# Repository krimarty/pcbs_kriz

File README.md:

# pcbs_kriz
Repository for all of Martin's PCBs

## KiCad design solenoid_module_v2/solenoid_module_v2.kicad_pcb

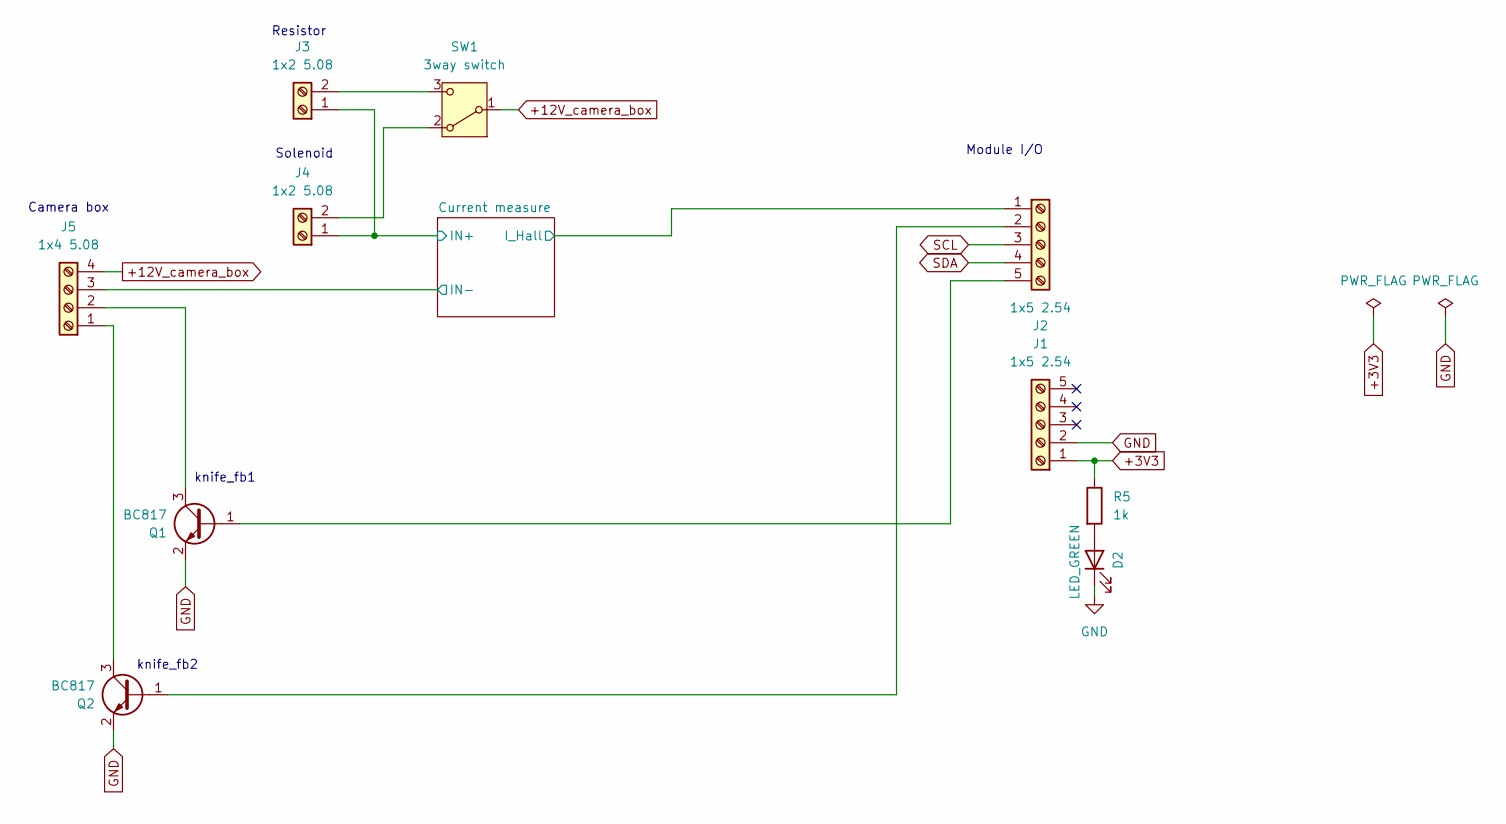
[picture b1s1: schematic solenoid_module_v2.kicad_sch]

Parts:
D2: LED_GREEN; LED_0805_2012Metric_Pad1.15x1.40mm_HandSolder; Manufacturer Part Number APTD2012LCGCK; Mouser number 604-APTD2012LCGCK
J1, J2: 1x5 2.54; PinHeader_1x05_P2.54mm_Vertical; Manufacturer Part Number 68000-420HLF; Mouser Part Number 649-68000-420HLF
J3, J4: 1x2 5.08; TerminalBlock_MetzConnect_Type101_RT01602HBWC_1x02_P5.08mm_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; Manufacturer Part Number TB0012-508-02GR; Mouser Part Number 179-TB0012-508-02GR
J5: 1x4 5.08; TerminalBlock_MetzConnect_Type101_RT01604HBWC_1x04_P5.08mm_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; Manufacturer Part Number TB0012-508-02GR; Mouser Part Number 179-TB0012-508-02GR
Q1, Q2: BC817; SOT-23; Manufacturer Part Number BC817; Mouser Part Number 583-BC817
R5: 1k; R_0603_1608Metric_Pad0.98x0.95mm_HandSolder; Manufacturer Part Number RC0603FR-071KL; Mouser number 603-RC0603FR-071KL
SW1: 3way switch; SW_Slide-03_Wuerth-WS-SLTV_10x2.5x6.4_P2.54mm; Manufacturer Part Number 200AWMSP3T2A1M2QE; Mouser Part Number 612-200AWMSP3T2A1M2Q

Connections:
+3V3: J1.1, R5.1; also elsewhere on the board
+12V_camera_box: J5.4, SW1.1 (B)
/Current measure/IN+: J3.1, J4.1; also elsewhere on the board
/Current measure/IN-: J5.3; also elsewhere on the board
/Current measure/I_Hall: J2.1; also elsewhere on the board
GND: D2.1 (K), J1.2, Q1.2 (E), Q2.2 (E); also elsewhere on the board
unnamed: D2.2 (A), R5.2
unnamed: J2.2, Q2.1 (B)
unnamed: J2.5, Q1.1 (B)
unnamed: J3.2, SW1.3 (C)
unnamed 10: J4.2, SW1.2 (A); also elsewhere on the board
unnamed: J5.1, Q2.3 (C)
unnamed: J5.2, Q1.3 (C)
SCL: J2.3
SDA: J2.4

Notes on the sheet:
Solenoid
knife_fb1
knife_fb2
Module I/O
Resistor
Camera box

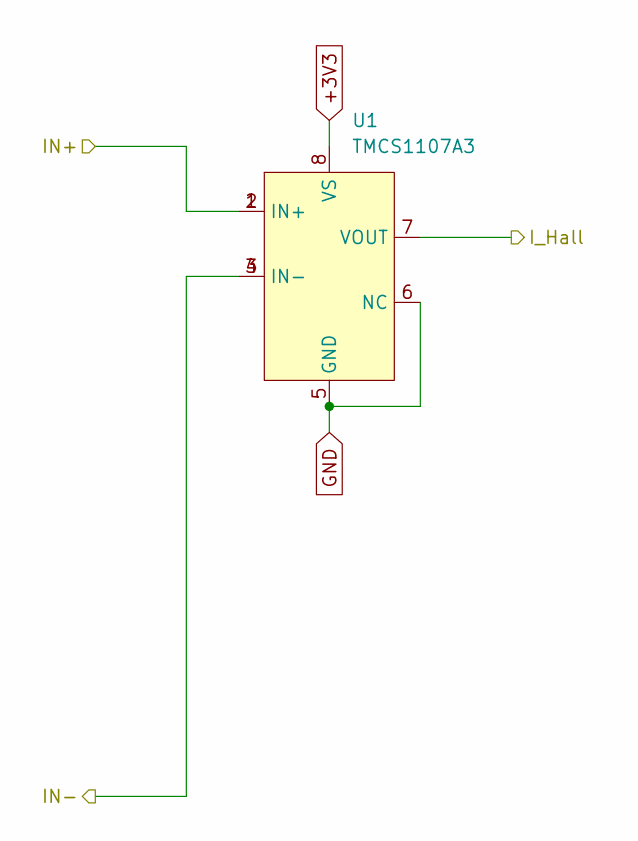
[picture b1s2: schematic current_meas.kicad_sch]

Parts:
U1: TMCS1107A3; SOIC-8_3.9x4.9mm_P1.27mm; Manufacturer Part Number TMCS1107A3UQDR; Mouser Part Number 595-TMCS1107A3UQDR

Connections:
+3V3: U1.8 (VS); also elsewhere on the board
/Current measure/IN+: U1.1 (IN+), U1.2 (IN+); also elsewhere on the board
/Current measure/IN-: U1.3 (IN-), U1.4 (IN-); also elsewhere on the board
/Current measure/I_Hall: U1.7 (VOUT); also elsewhere on the board
GND: U1.5 (GND), U1.6 (NC); also elsewhere on the board

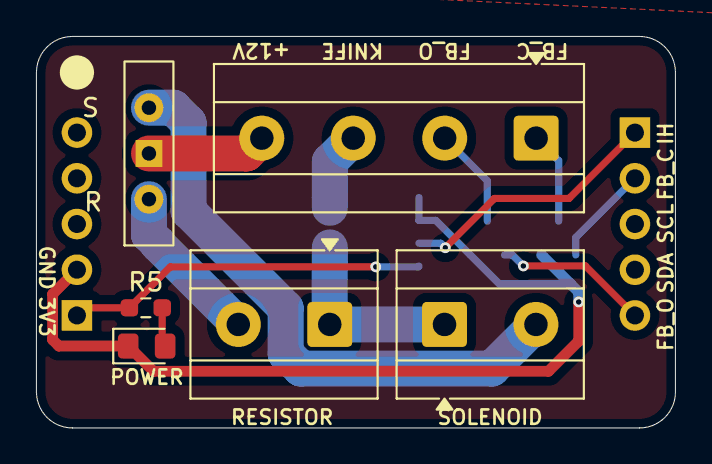
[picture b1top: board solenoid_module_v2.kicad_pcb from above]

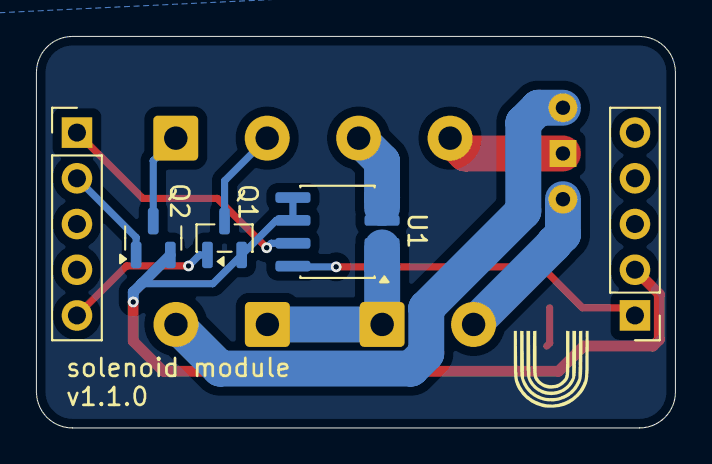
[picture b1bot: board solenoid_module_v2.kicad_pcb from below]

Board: 2 copper layers, 35.5 x 21.8 mm, 11 parts (5 on the bottom side), 13 nets.

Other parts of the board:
RESISTOR: 1x2 5.08; TerminalBlock_MetzConnect_Type101_RT01602HBWC_1x02_P5.08mm_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

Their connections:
/Current measure/IN+: RESISTOR.1; also elsewhere on the board
unnamed 10: RESISTOR.2; also elsewhere on the board

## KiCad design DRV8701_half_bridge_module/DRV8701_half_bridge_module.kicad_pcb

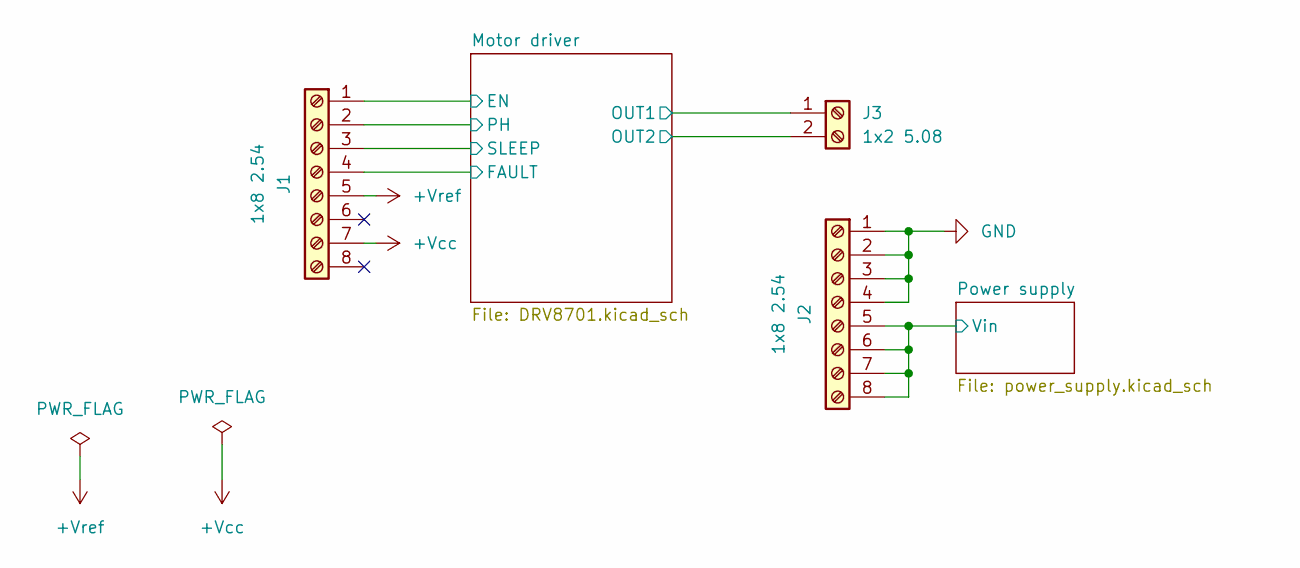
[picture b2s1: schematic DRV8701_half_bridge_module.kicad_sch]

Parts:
J1, J2: 1x8 2.54; PinHeader_1x08_P2.54mm_Vertical; Manufacturer Part Number 68000-420HLF; Mouser number 649-68000-420HLF
J3: 1x2 5.08; TerminalBlock_RND_205-00232_1x02_P5.08mm_Horizontal; Manufacturer Part Number TB0012-508-02GR; Mouser number 179-TB0012-508-02GR

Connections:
+Vcc: J1.7; also elsewhere on the board
+Vref: J1.5
/Motor driver/EN: J1.1; also elsewhere on the board
/Motor driver/FAULT: J1.4; also elsewhere on the board
/Motor driver/OUT1: J3.1; also elsewhere on the board
/Motor driver/PH: J1.2; also elsewhere on the board
/Motor driver/SLEEP: J1.3; also elsewhere on the board
/Power supply/Vin: J2.5, J2.6, J2.7, J2.8; also elsewhere on the board
GND: J2.1, J2.2, J2.3, J2.4, J3.2; also elsewhere on the board

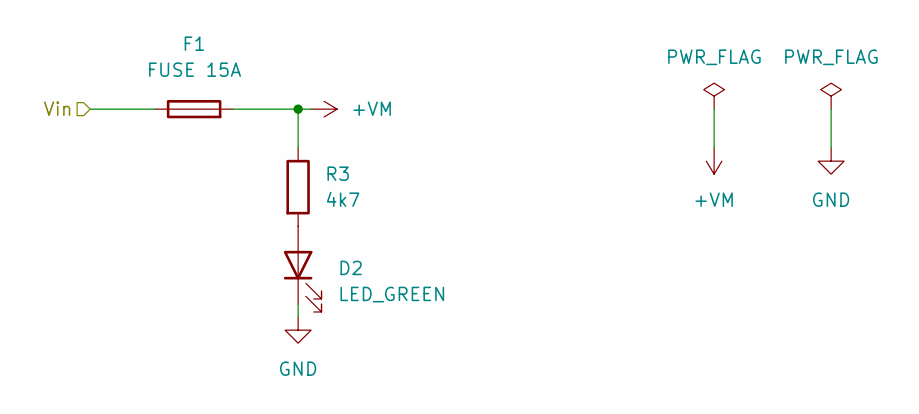
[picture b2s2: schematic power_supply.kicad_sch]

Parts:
D2: LED_GREEN; LED_0805_2012Metric_Pad1.15x1.40mm_HandSolder; Manufacturer Part Number APTD2012LCGCK; Mouser number 604-APTD2012LCGCK
F1: FUSE 15A; Fuseholder_Blade_Mini_Keystone_3568; Manufacturer Part Number 3568; Mouser number 534-3568
R3: 4k7; R_0603_1608Metric_Pad0.98x0.95mm_HandSolder; Manufacturer Part Number RC0603FR-074K7L; Mouser number 603-RC0603FR-074K7L

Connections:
+VM: F1.2, R3.1; also elsewhere on the board
/Power supply/Vin: F1.1; also elsewhere on the board
GND: D2.1 (K); also elsewhere on the board
unnamed: D2.2 (A), R3.2

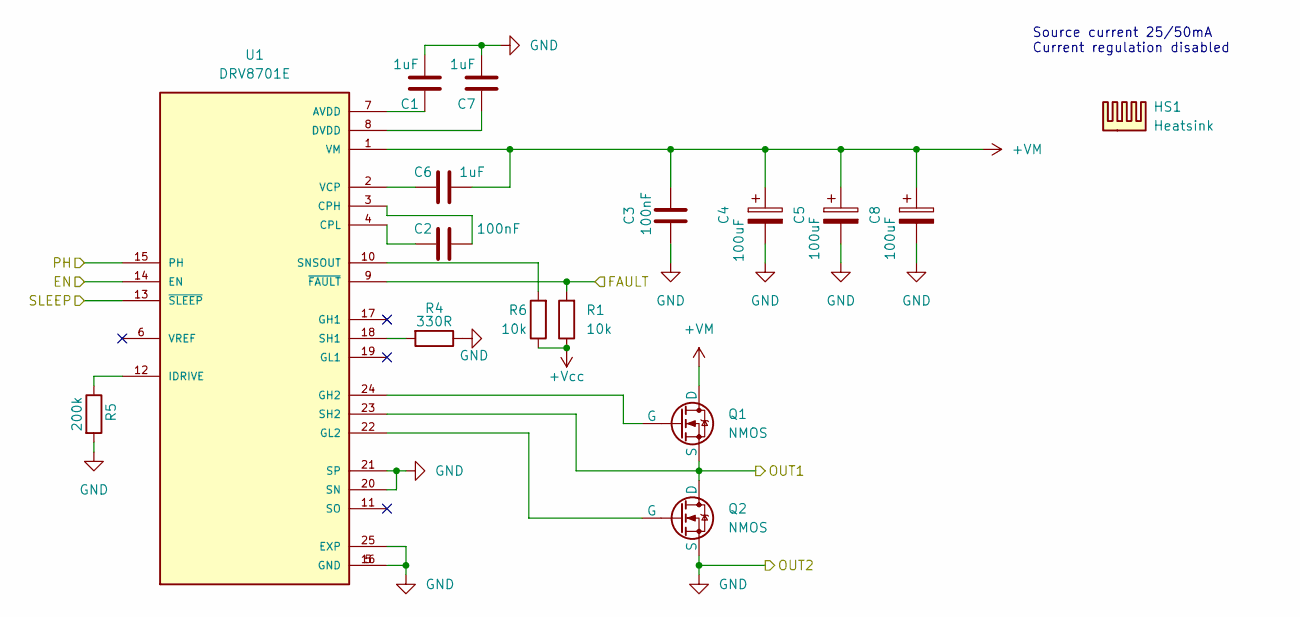
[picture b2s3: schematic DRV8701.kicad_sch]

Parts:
C1, C6, C7: 1uF; C_0603_1608Metric_Pad1.08x0.95mm_HandSolder; Manufacturer Part Number CC603KRX5R8BB105; Mouser number 603-CC603KRX5R8BB105
C2, C3: 100nF; C_0603_1608Metric_Pad1.08x0.95mm_HandSolder; Manufacturer Part Number C0603C104M5RACTU; Mouser number 603-CC603KRX7R9BB103
C4, C5, C8: 100uF; CP_EIA-7343-40_Kemet-Y_HandSolder; Manufacturer Part Number 80-T491X107M25ATAUTO; Mouser number 80-T491X107M25ATAUTO
HS1: Heatsink; DRV8874_TO220_Heatsink; Manufacturer Part Number ICKSMDM21SA
Q1, Q2: NMOS; ONSemi_SO-8FL_488AA; Manufacturer Part Number NVMFWS1D7N04XMT1G; Mouser number 863-VMFWS1D7N04XMT1G
R1, R6: 10k; R_0603_1608Metric_Pad0.98x0.95mm_HandSolder; Manufacturer Part Number RC0603FR-0710KL; Mouser number 603-RC0603FR-0710KL
R4: 330R; R_0603_1608Metric_Pad0.98x0.95mm_HandSolder; Manufacturer Part Number RT0603FRE13330RL; Mouser number 603-RT0603FRE13330RL
R5: 200k; R_0603_1608Metric_Pad0.98x0.95mm_HandSolder; Manufacturer Part Number RT0603FRE07200KL; Mouser number 603-RT0603FRE07200KL
U1: DRV8701E; QFN50P400X400X100-25N; PARTREV B; Mouser number 595-DRV8701ERGER

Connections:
+VM: C3.1, C4.1, C5.1, C6.1, C8.1, Q1.1 (D), U1.1 (VM); also elsewhere on the board
+Vcc: R1.1, R6.1; also elsewhere on the board
/Motor driver/EN: U1.14 (EN); also elsewhere on the board
/Motor driver/FAULT: R1.2, U1.9 (~FAULT); also elsewhere on the board
/Motor driver/OUT1: Q1.3 (S), Q2.1 (D), U1.23 (SH2); also elsewhere on the board
/Motor driver/PH: U1.15 (PH); also elsewhere on the board
/Motor driver/SLEEP: U1.13 (~SLEEP); also elsewhere on the board
GND: C1.1, C3.2, C4.2, C5.2, C7.1, C8.2, Q2.3 (S), R4.1, R5.2, U1.5 (GND), U1.16 (GND), U1.20 (SN), U1.21 (SP), U1.25 (EXP); also elsewhere on the board
unnamed: Q1.2 (G), U1.24 (GH2)
unnamed: Q2.2 (G), U1.22 (GL2)
unnamed: C1.2, U1.7 (AVDD)
unnamed: C2.1, U1.3 (CPH)
unnamed: C2.2, U1.4 (CPL)
unnamed: C7.2, U1.8 (DVDD)
unnamed: R5.1, U1.12 (IDRIVE)
unnamed: R4.2, U1.18 (SH1)
unnamed: R6.2, U1.10 (SNSOUT)
unnamed: C6.2, U1.2 (VCP)

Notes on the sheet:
Source current 25/50mA Current regulation disabled

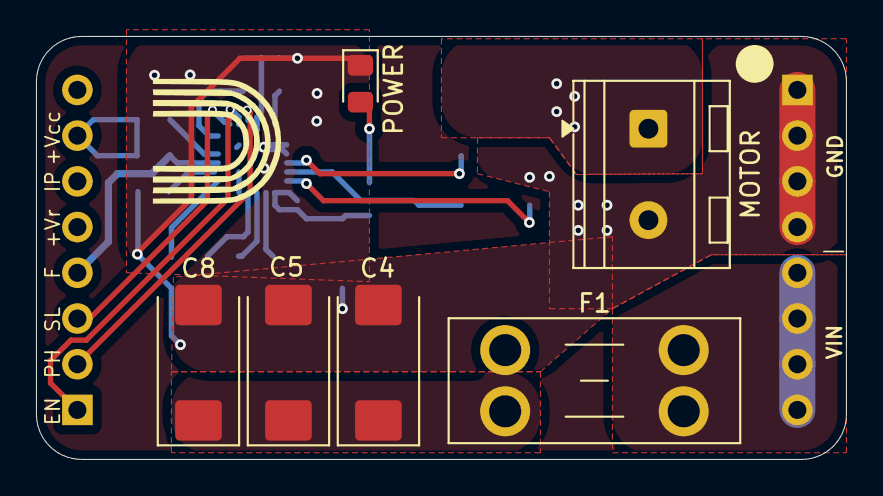
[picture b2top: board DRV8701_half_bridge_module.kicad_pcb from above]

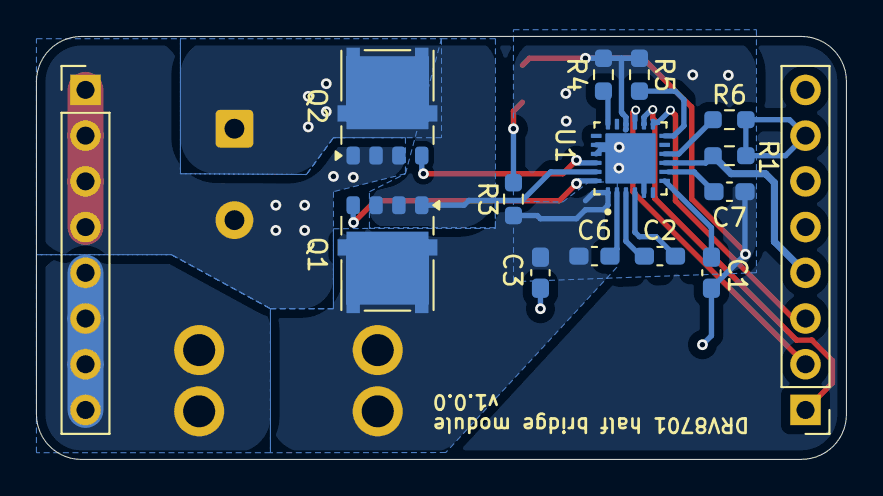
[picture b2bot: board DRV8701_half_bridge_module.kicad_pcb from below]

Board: 2 copper layers, 45.0 x 23.5 mm, 21 parts (15 on the bottom side), 20 nets.

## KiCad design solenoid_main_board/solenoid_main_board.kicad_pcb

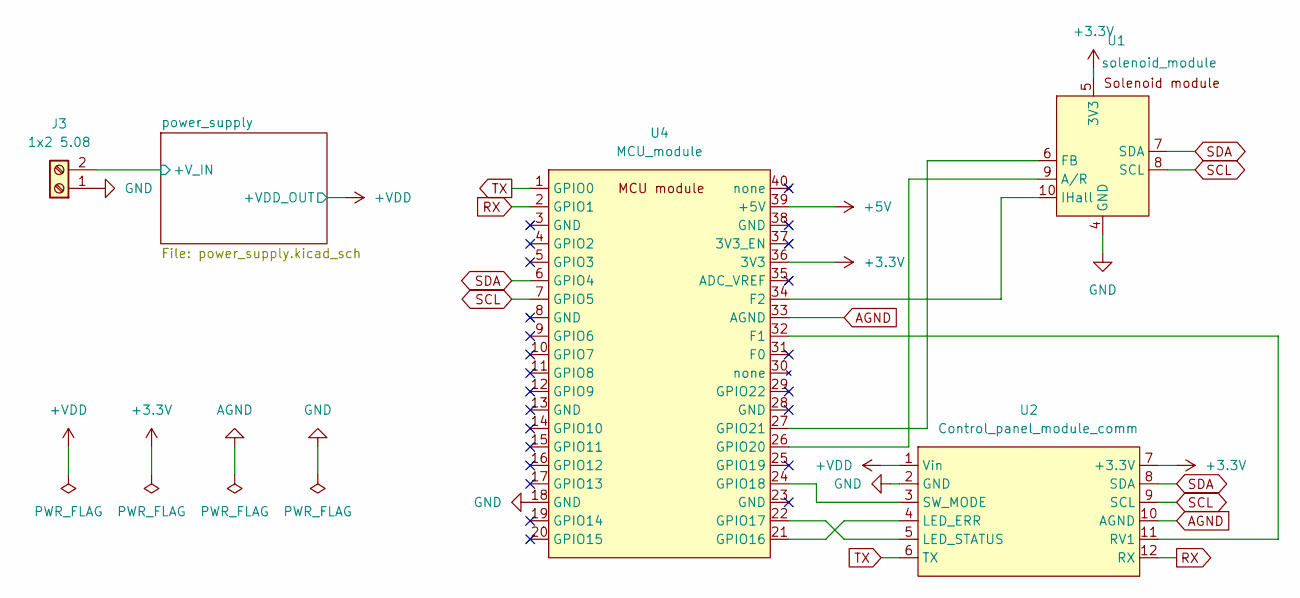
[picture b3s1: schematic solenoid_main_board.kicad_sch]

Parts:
J3: 1x2 5.08; TerminalBlock_MetzConnect_Type101_RT01602HBWC_1x02_P5.08mm_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; Manufacturer Part Number TB0012-508-02GR; Mouser Part Number 179-TB0012-508-02GR
U1: solenoid_module
U2: Control_panel_module_comm; control_panel_module
U4: MCU_module

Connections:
+3.3V: U1.5 (3V3), U2.7 (+3.3V), U4.36 (3V3)
+5V: U4.39 (+5V); also elsewhere on the board
+VDD: U2.1 (Vin); also elsewhere on the board
/power_supply/+V_IN: J3.2; also elsewhere on the board
AGND: U2.10 (AGND), U4.33 (AGND)
GND: J3.1, U1.4 (GND), U2.2 (GND), U4.18 (GND); also elsewhere on the board
unnamed: U1.9 (A/R), U4.26 (GPIO20)
unnamed: U1.6 (FB), U4.27 (GPIO21)
unnamed: U1.10 (IHall), U4.34 (F2)
unnamed: U2.4 (LED_ERR), U4.21 (GPIO16)
unnamed: U2.5 (LED_STATUS), U4.22 (GPIO17)
unnamed: U2.11 (RV1), U4.32 (F1)
unnamed: U2.3 (SW_MODE), U4.24 (GPIO18)
RX: U2.12 (RX), U4.2 (GPIO1)
SCL: U1.8 (SCL), U2.9 (SCL), U4.7 (GPIO5)
SDA: U1.7 (SDA), U2.8 (SDA), U4.6 (GPIO4)
TX: U2.6 (TX), U4.1 (GPIO0)

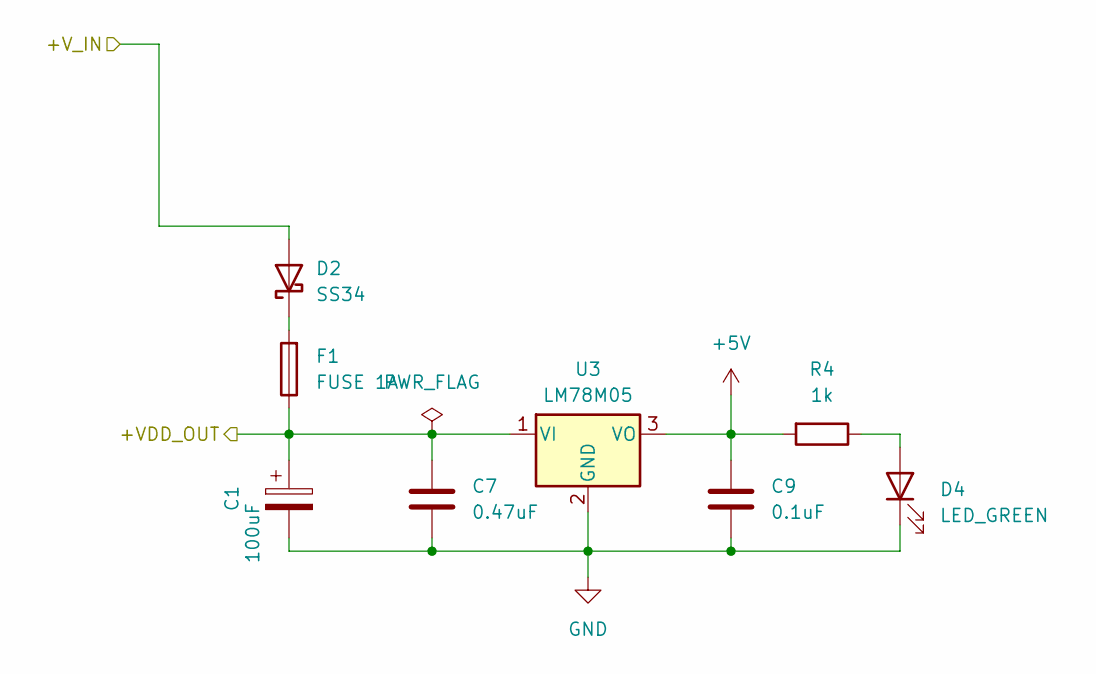
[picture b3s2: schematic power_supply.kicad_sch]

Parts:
C1: 100uF; CP_EIA-7343-40_Kemet-Y_HandSolder; Manufacturer Part Number T491X107M025ATAUTO; Mouser Part Number 80-T491X107M25ATAUTO
C7: 0.47uF; C_0603_1608Metric_Pad1.08x0.95mm_HandSolder; Manufacturer Part Number C1608X5R1C475KE; Mouser Part Number 810-C1608X5R1C475KE
C9: 0.1uF; C_0603_1608Metric_Pad1.08x0.95mm_HandSolder; Manufacturer Part Number C0603C104M5RACTU; Mouser Part Number 80-C0603C104M5R
D2: SS34; D_SMB-SMC_Universal_Handsoldering; Manufacturer Part Number SS34; Mouser Part Number 512-SS34
D4: LED_GREEN; LED_0805_2012Metric_Pad1.15x1.40mm_HandSolder; Manufacturer Part Number APTD2012LCGCK; Mouser Part Number 604-APTD2012LCGCK
F1: FUSE 1A; Fuseholder_Blade_Mini_Keystone_3568; Manufacturer Part Number 3568; Mouser Part Number 534-3568
R4: 1k; R_0603_1608Metric_Pad0.98x0.95mm_HandSolder; Manufacturer Part Number RC0603FR-071KL; Mouser Part Number 603-RC0603FR-071KL
U3: LM78M05; TO-252-2; Manufacturer Part Number L78M05CDT-TR; Mouser Part Number 511-L78M05CDT-TR

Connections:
+5V: C9.1, R4.2, U3.3 (VO); also elsewhere on the board
+VDD: C1.1, C7.1, F1.1, U3.1 (VI); also elsewhere on the board
/power_supply/+V_IN: D2.2 (A); also elsewhere on the board
GND: C1.2, C7.2, C9.2, D4.1 (K), U3.2 (GND); also elsewhere on the board
unnamed: D2.1 (K), F1.2
unnamed: D4.2 (A), R4.1

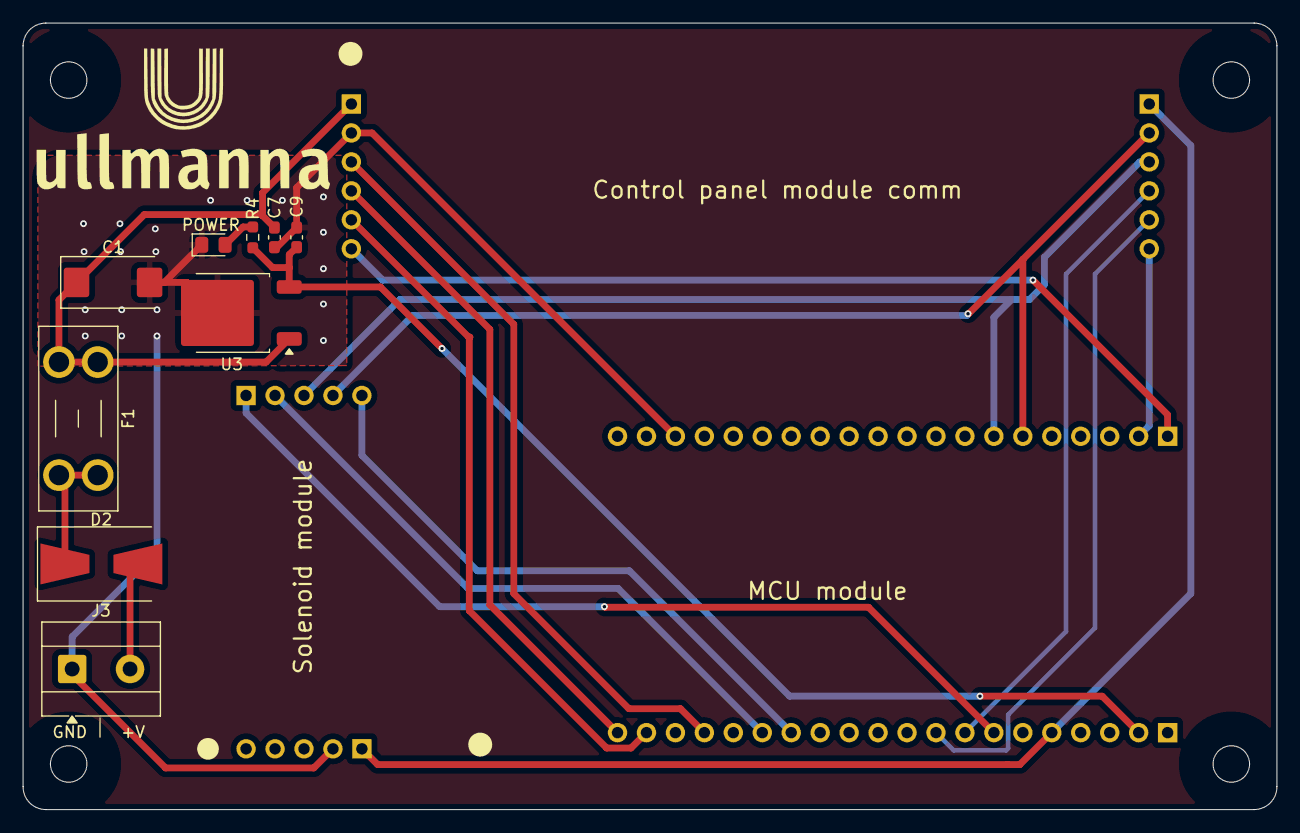
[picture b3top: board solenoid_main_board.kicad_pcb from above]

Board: 2 copper layers, 110.0 x 69.0 mm, 16 parts (0 on the bottom side), 19 nets.

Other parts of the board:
H3, H3#2, H3#3, H3#4: MountingHole; MountingHole_3.2mm_M3

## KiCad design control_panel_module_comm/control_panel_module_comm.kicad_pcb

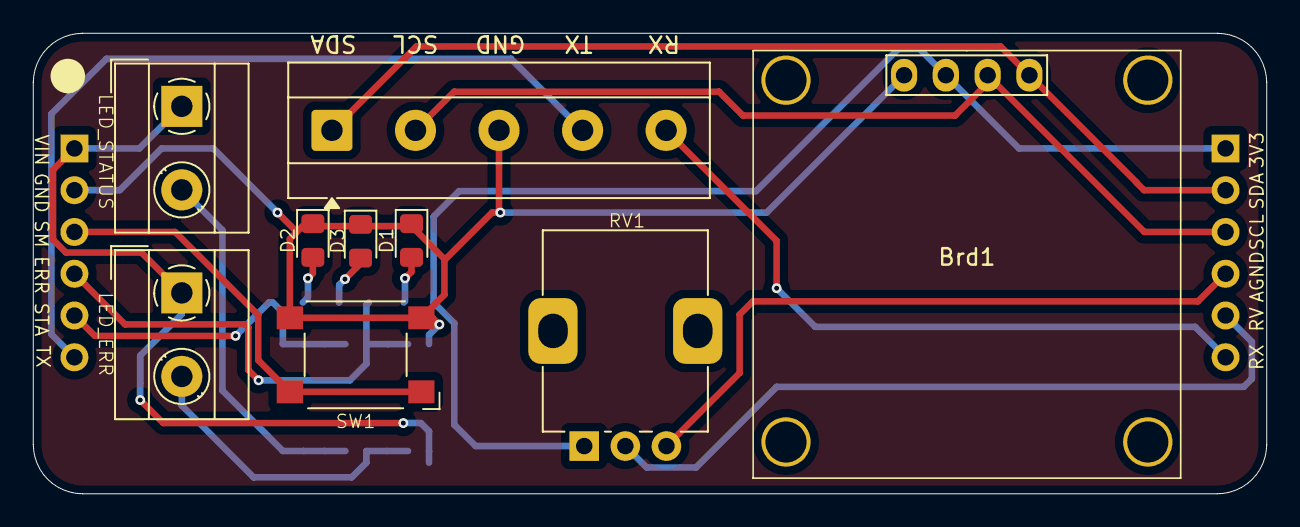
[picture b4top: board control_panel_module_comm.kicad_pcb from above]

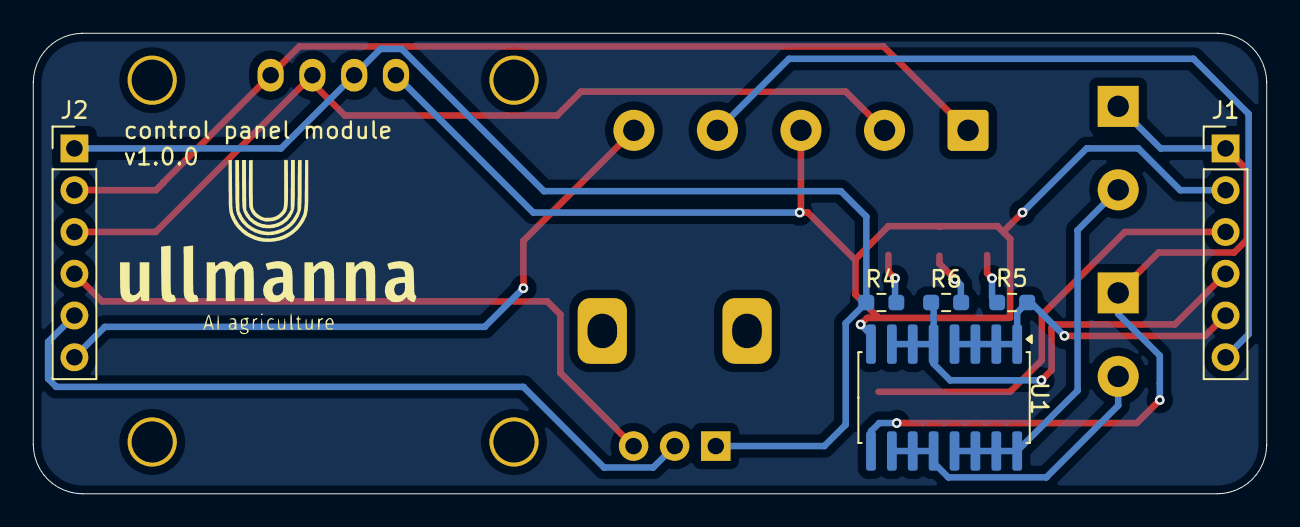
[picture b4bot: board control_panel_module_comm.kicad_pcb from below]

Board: 2 copper layers, 75.0 x 28.0 mm, 15 parts (6 on the bottom side), 17 nets.

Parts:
Brd1: SSD1306; 128x64OLED
D1: LED_GREEN; LED_0805_2012Metric_Pad1.15x1.40mm_HandSolder
D2: LED_ORANGE; LED_0805_2012Metric_Pad1.15x1.40mm_HandSolder
D3: LED_RED; LED_0805_2012Metric_Pad1.15x1.40mm_HandSolder
J1, J2: 1x6 2.54; PinHeader_1x06_P2.54mm_Vertical
J3: 1x2 5.08; TerminalBlock_MetzConnect_Type101_RT01602HBWC_1x02_P5.08mm_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
J4: 1x3 5.08; TerminalBlock_MetzConnect_Type101_RT01602HBWC_1x02_P5.08mm_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
J5: 1x5 5.08; TerminalBlock_MetzConnect_Type101_RT01605HBWC_1x05_P5.08mm_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
R4, R5, R6: 1k; R_0603_1608Metric_Pad0.98x0.95mm_HandSolder
RV1: 100k; Potentiometer_Alps_RK09K_Single_Vertical
SW1: BTN; SW_SPST_Omron_B3FS-105xP
U1: ULN2004A; SOIC-16W_5.3x10.2mm_P1.27mm

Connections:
+3.3V: Brd1.2 (VCC), J2.1, R4.1, RV1.1
+Vin: J1.1, J3.1, J4.1, U1.9 (COM)
/Buttons/RV_SPEED: J2.5, RV1.2
/Buttons/SW_MODE: J1.3, SW1.1 (A)
/Communication/RX: J2.6, J5.5
/Communication/SCL: Brd1.3 (SCL), J2.3, J5.2
/Communication/SDA: Brd1.4 (SDA), J2.2, J5.1
/Communication/TX: J1.6, J5.4
/Indicators/ERR: J1.4, R6.1, U1.5 (I5), U1.6 (I6), U1.7 (I7)
/Indicators/STATUS: J1.5, R5.1, U1.1 (I1), U1.2 (I2), U1.3 (I3), U1.4 (I4)
AGND: J2.4, RV1.3
GND: Brd1.1 (GND), D1.1 (K), D2.1 (K), D3.1 (K), J1.2, J5.3, SW1.2 (B), U1.8 (GND)
unnamed: D1.2 (A), R4.2
unnamed: D2.2 (A), R5.2
unnamed: D3.2 (A), R6.2
unnamed: J3.2, U1.13 (O4), U1.14 (O3), U1.15 (O2), U1.16 (O1)
unnamed: J4.2, U1.10 (O7), U1.11 (O6), U1.12 (O5)

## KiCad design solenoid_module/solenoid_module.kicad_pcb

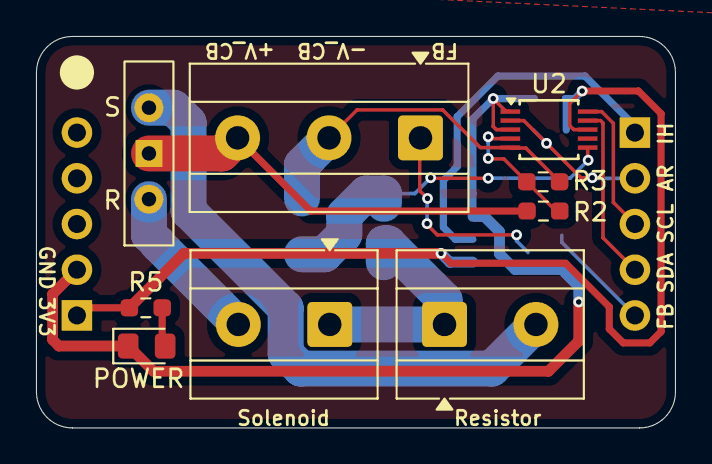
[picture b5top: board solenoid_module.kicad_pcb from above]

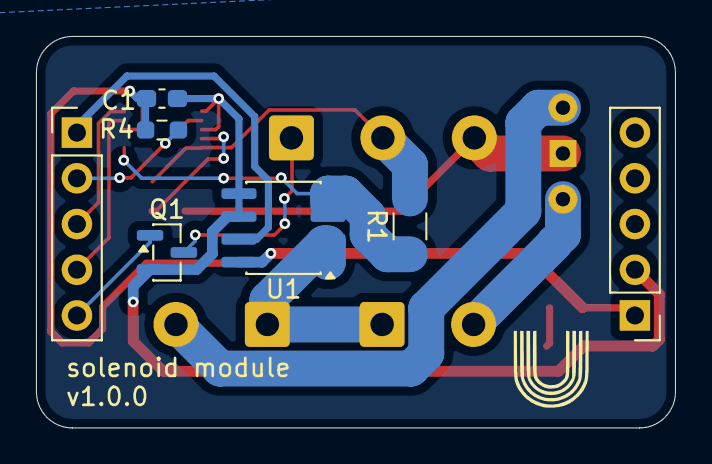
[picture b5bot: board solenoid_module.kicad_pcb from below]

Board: 2 copper layers, 35.5 x 21.8 mm, 16 parts (7 on the bottom side), 16 nets.

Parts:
C1: 0.1 uF; C_0603_1608Metric_Pad1.08x0.95mm_HandSolder
J1, J2: 1x5 2.54; PinHeader_1x05_P2.54mm_Vertical
J5: 1x3 5.08; TerminalBlock_MetzConnect_Type101_RT01603HBWC_1x03_P5.08mm_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
POWER: LED_GREEN; LED_0805_2012Metric_Pad1.15x1.40mm_HandSolder
Q1: BC817; SOT-23
R1: R01; R_1206_3216Metric_Pad1.30x1.75mm_HandSolder
R2: 10K; R_0603_1608Metric_Pad0.98x0.95mm_HandSolder
R3: 3K3; R_0603_1608Metric_Pad0.98x0.95mm_HandSolder
R4: 10k; R_0603_1608Metric_Pad0.98x0.95mm_HandSolder
R5: 1k; R_0603_1608Metric_Pad0.98x0.95mm_HandSolder
Resistor: 1x2 5.08; TerminalBlock_MetzConnect_Type101_RT01602HBWC_1x02_P5.08mm_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
SW1: 3way switch; SW_Slide-03_Wuerth-WS-SLTV_10x2.5x6.4_P2.54mm
Solenoid: 1x2 5.08; TerminalBlock_MetzConnect_Type101_RT01602HBWC_1x02_P5.08mm_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
U1: TMCS1107A3; SOIC-8_3.9x4.9mm_P1.27mm
U2: ADS1115IDGS; TSSOP-10_3x3mm_P0.5mm

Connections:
+3V3: C1.1, J1.1, R4.2, R5.1, U1.8 (VS), U2.8 (VDD)
+12V_camera_box: J5.3, R2.1, SW1.1 (B)
/ADC/A0: R2.2, R3.1, U2.4 (AIN0)
/ADC/A1: J5.2, R1.2, R3.2, U2.5 (AIN1)
/ADC/A2: R1.1, U1.3 (IN-), U1.4 (IN-), U2.6 (AIN2)
/ADC/ALERT/READY: J2.2, R4.1, U2.2 (ALERT/RDY)
/Current measure/IN+: Resistor.1, Solenoid.1, U1.1 (IN+), U1.2 (IN+)
/Current measure/I_Hall: J2.1, U1.7 (VOUT)
GND: C1.2, J1.2, POWER.1 (K), Q1.2 (E), U1.5 (GND), U1.6 (NC), U2.1 (ADDR), U2.3 (GND)
unnamed: POWER.2 (A), R5.2
unnamed: J2.5, Q1.1 (B)
unnamed: Resistor.2, SW1.3 (C)
unnamed: SW1.2 (A), Solenoid.2
unnamed: J5.1, Q1.3 (C)
SCL: J2.3, U2.10 (SCL)
SDA: J2.4, U2.9 (SDA)

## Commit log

2025-10-11 add solenoid module
2025-10-11 Solenoid module wiring
2025-10-13 solenoid module pcb layout
2025-10-13 Solenoid module v1.0.0
2025-10-13 Control_panel_module_comm upload
2025-10-14 solenoid_main_board schematic
2025-10-20 main board layout
2025-10-21 Solenoid main board finished
2025-10-23 PCB update
2025-10-25 Add half bridge schematic
2025-10-26 Half bridge layout with errors
2025-10-27 Half bridge error fixed
2025-12-22 Add second version of solenoid module
2025-12-26 Solenoid moduke new ver
